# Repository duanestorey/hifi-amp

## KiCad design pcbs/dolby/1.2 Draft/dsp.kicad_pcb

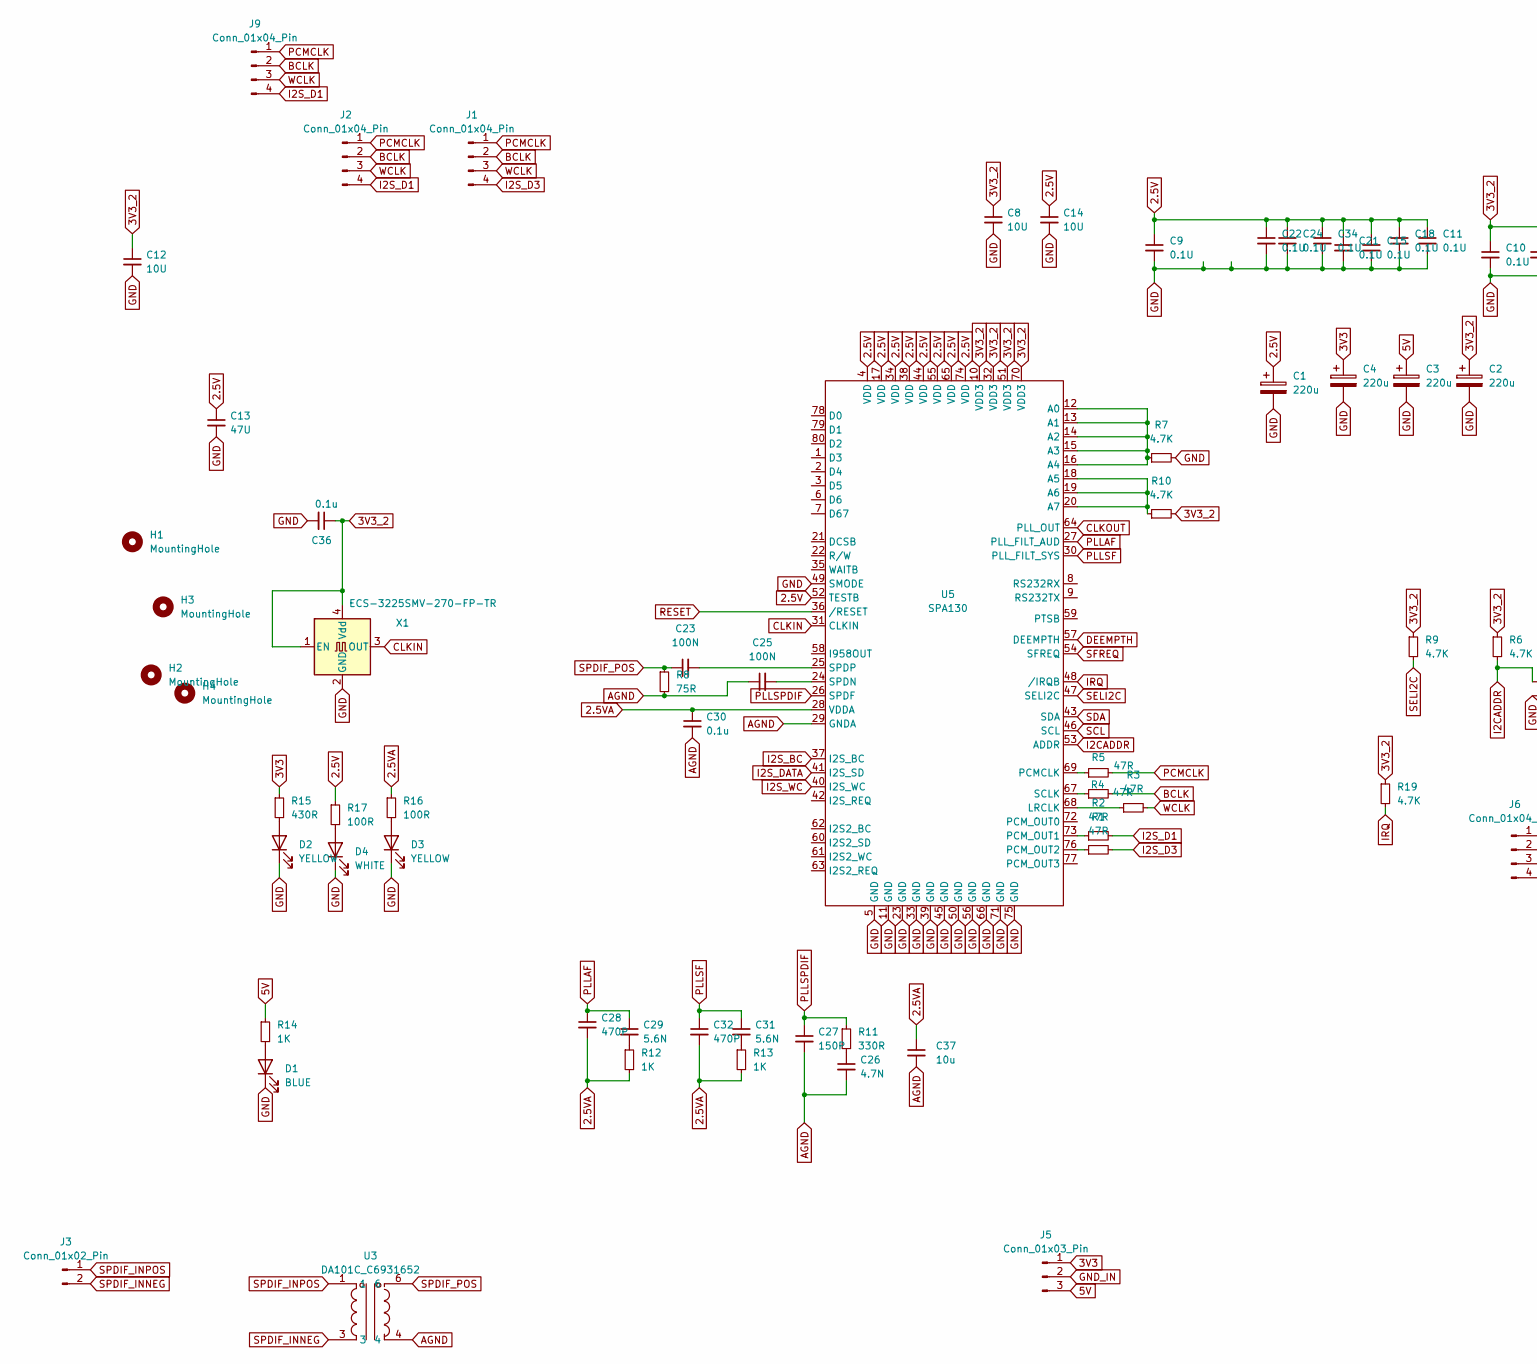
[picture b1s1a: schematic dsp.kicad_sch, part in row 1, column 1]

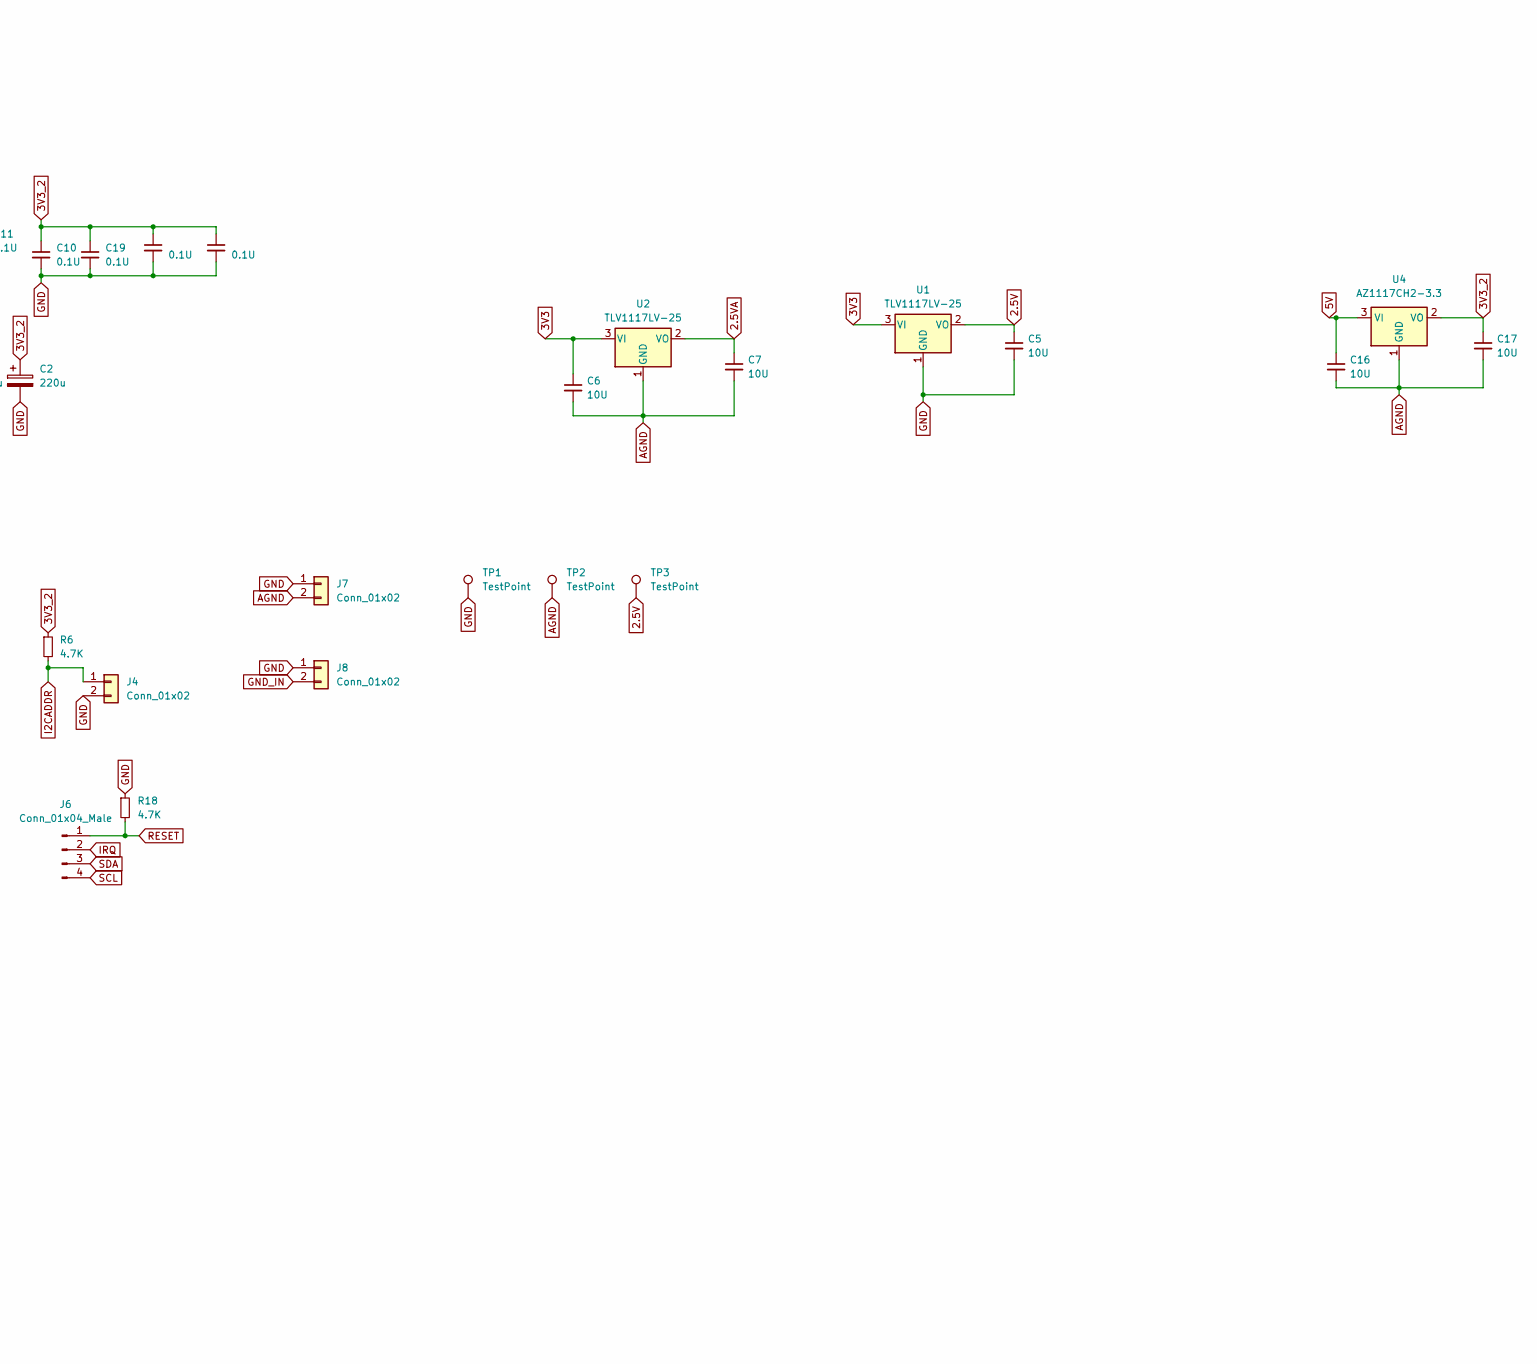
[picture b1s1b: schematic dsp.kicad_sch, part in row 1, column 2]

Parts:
C1, C2, C3, C4: 220u; CP_Radial_D6.3mm_P2.50mm
C5, C6, C7, C8, C12, C14, C16, C17: 10U; C_1206_3216Metric_Pad1.33x1.80mm_HandSolder
C9, C10, C11, C15, C18, C19, C20, C21, C22, C24, C33, C34: 0.1U; C_0805_2012Metric_Pad1.18x1.45mm_HandSolder
C13: 47U; C_1206_3216Metric_Pad1.33x1.80mm_HandSolder
C23, C25: 100N; C_0805_2012Metric_Pad1.18x1.45mm_HandSolder
C26: 4.7N; C_0805_2012Metric_Pad1.18x1.45mm_HandSolder
C27: 150P; C_0805_2012Metric_Pad1.18x1.45mm_HandSolder
C28, C32: 470P; C_0805_2012Metric_Pad1.18x1.45mm_HandSolder
C29, C31: 5.6N; C_0805_2012Metric_Pad1.18x1.45mm_HandSolder
C30, C36: 0.1u; C_0805_2012Metric_Pad1.18x1.45mm_HandSolder
C37: 10u; C_1206_3216Metric_Pad1.33x1.80mm_HandSolder
D1: BLUE; LED_0805_2012Metric_Pad1.15x1.40mm_HandSolder
D2, D3: YELLOW; LED_0805_2012Metric_Pad1.15x1.40mm_HandSolder
D4: WHITE; LED_0805_2012Metric_Pad1.15x1.40mm_HandSolder
H1, H2, H3, H4: MountingHole; MountingHole_3.2mm_M3_DIN965_Pad_TopBottom
J1, J2: Conn_01x04_Pin; JST_PH_B4B-PH-K_1x04_P2.00mm_Vertical
J3: Conn_01x02_Pin; JST_XH_B2B-XH-A_1x02_P2.50mm_Vertical
J4, J7, J8: Conn_01x02; PinHeader_1x02_P2.54mm_Vertical
J5: Conn_01x03_Pin; JST_PH_B3B-PH-K_1x03_P2.00mm_Vertical
J6: Conn_01x04_Male; JST_PH_B4B-PH-K_1x04_P2.00mm_Vertical
J9: Conn_01x04_Pin; PinHeader_1x04_P2.54mm_Vertical
R1, R2, R3, R4, R5: 47R; R_0805_2012Metric_Pad1.20x1.40mm_HandSolder
R6, R7, R9, R10, R18, R19: 4.7K; R_0603_1608Metric_Pad0.98x0.95mm_HandSolder
R8: 75R; R_0603_1608Metric_Pad0.98x0.95mm_HandSolder
R11: 330R; R_0603_1608Metric_Pad0.98x0.95mm_HandSolder
R12, R13, R14: 1K; R_0603_1608Metric_Pad0.98x0.95mm_HandSolder
R15: 430R; R_0603_1608Metric_Pad0.98x0.95mm_HandSolder
R16, R17: 100R; R_0603_1608Metric_Pad0.98x0.95mm_HandSolder
TP1, TP2, TP3: TestPoint; TestPoint_THTPad_1.5x1.5mm_Drill0.7mm
U1, U2: TLV1117LV-25; SOT-223-3_TabPin2
U3: DA101C_C6931652; XFMR-TH_4P-L9.5-W9.0-P5.08-LS10.2_C9900096976; LCSC Part C6931652
U4: AZ1117CH2-3.3; SOT-223-3_TabPin2
U5: SPA130; LQFP-80_14x14mm_P0.65mm
X1: ECS-3225SMV-270-FP-TR; Oscillator_SMD_EuroQuartz_XO32-4Pin_3.2x2.5mm_HandSoldering

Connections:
2.5V: C1.1, C5.1, C9.1, C11.1, C13.1, C14.1, C15.1, C18.1, C21.1, C22.1, C24.1, C34.1, R17.1, TP3.1, U1.2 (VO), U5.4 (VDD), U5.17 (VDD), U5.34 (VDD), U5.38 (VDD), U5.44 (VDD), U5.52 (TESTB), U5.55 (VDD), U5.65 (VDD), U5.74 (VDD)
2.5VA: C7.1, C28.2, C30.1, C32.2, C37.1, R12.2, R13.2, R16.1, U2.2 (VO), U5.28 (VDDA)
3V3: C4.1, C6.1, J5.1, R15.1, U1.3 (VI), U2.3 (VI)
3V3_2: C2.1, C8.1, C10.1, C12.1, C17.1, C19.1, C20.1, C33.1, C36.1, R6.1, R9.1, R10.2, R19.1, U4.2 (VO), U5.10 (VDD3), U5.32 (VDD3), U5.51 (VDD3), U5.70 (VDD3), X1.1 (EN), X1.4 (Vdd)
5V: C3.1, C16.1, J5.3, R14.1, U4.3 (VI)
AGND: C6.2, C7.2, C16.2, C17.2, C25.1, C26.2, C27.2, C30.2, C37.2, J7.2, R8.2, TP2.1, U2.1 (GND), U3.4, U4.1 (GND), U5.29 (GNDA)
BCLK: J1.2, J2.2, J9.2, R4.2
CLKIN: U5.31 (CLKIN), X1.3 (OUT)
CLKOUT: U5.64 (PLL_OUT)
DEEMPTH: U5.57 (DEEMPTH)
GND: C1.2, C2.2, C3.2, C4.2, C5.2, C8.2, C9.2, C10.2, C11.2, C12.2, C13.2, C14.2, C15.2, C18.2, C19.2, C20.2, C21.2, C22.2, C24.2, C33.2, C34.2, C36.2, D1.1 (K), D2.1 (K), D3.1 (K), D4.1 (K), J4.2, J7.1, J8.1, R7.2, R18.1, TP1.1, U1.1 (GND), U5.5 (GND), U5.11 (GND), U5.23 (GND), U5.33 (GND), U5.39 (GND), U5.45 (GND), U5.49 (SMODE), U5.50 (GND), U5.56 (GND), U5.66 (GND), U5.71 (GND), U5.75 (GND), X1.2 (GND)
GND_IN: J5.2, J8.2
I2CADDR: J4.1, R6.2, U5.53 (ADDR)
I2S_BC: U5.37 (I2S_BC)
I2S_D1: J2.4, J9.4, R2.2
I2S_D3: J1.4, R1.2
I2S_DATA: U5.41 (I2S_SD)
I2S_WC: U5.40 (I2S_WC)
IRQ: J6.2, R19.2, U5.48 (/IRQB)
unnamed: C26.1, R11.2
unnamed: C29.2, R12.1
unnamed: C31.2, R13.1
unnamed: D1.2 (A), R14.2
unnamed: D2.2 (A), R15.2
unnamed: D3.2 (A), R16.2
unnamed: D4.2 (A), R17.2
unnamed: R7.1, U5.12 (A0), U5.13 (A1), U5.14 (A2), U5.15 (A3), U5.16 (A4)
unnamed: R10.1, U5.18 (A5), U5.19 (A6), U5.20 (A7)
unnamed: R3.1, U5.68 (LRCLK)
unnamed: R5.1, U5.69 (PCMCLK)
unnamed: R2.1, U5.73 (PCM_OUT1)
unnamed: R1.1, U5.76 (PCM_OUT2)
unnamed: R4.1, U5.67 (SCLK)
unnamed: C25.2, U5.24 (SPDN)
unnamed: C23.2, U5.25 (SPDP)
PCMCLK: J1.1, J2.1, J9.1, R5.2
PLLAF: C28.1, C29.1, U5.27 (PLL_FILT_AUD)
PLLSF: C31.1, C32.1, U5.30 (PLL_FILT_SYS)
PLLSPDIF: C27.1, R11.1, U5.26 (SPDF)
RESET: J6.1, R18.2, U5.36 (/RESET)
SCL: J6.4, U5.46 (SCL)
SDA: J6.3, U5.43 (SDA)
SELI2C: R9.2, U5.47 (SELI2C)
SFREQ: U5.54 (SFREQ)
SPDIF_INNEG: J3.2, U3.3
SPDIF_INPOS: J3.1, U3.1
SPDIF_POS: C23.1, R8.1, U3.6
WCLK: J1.3, J2.3, J9.3, R3.2

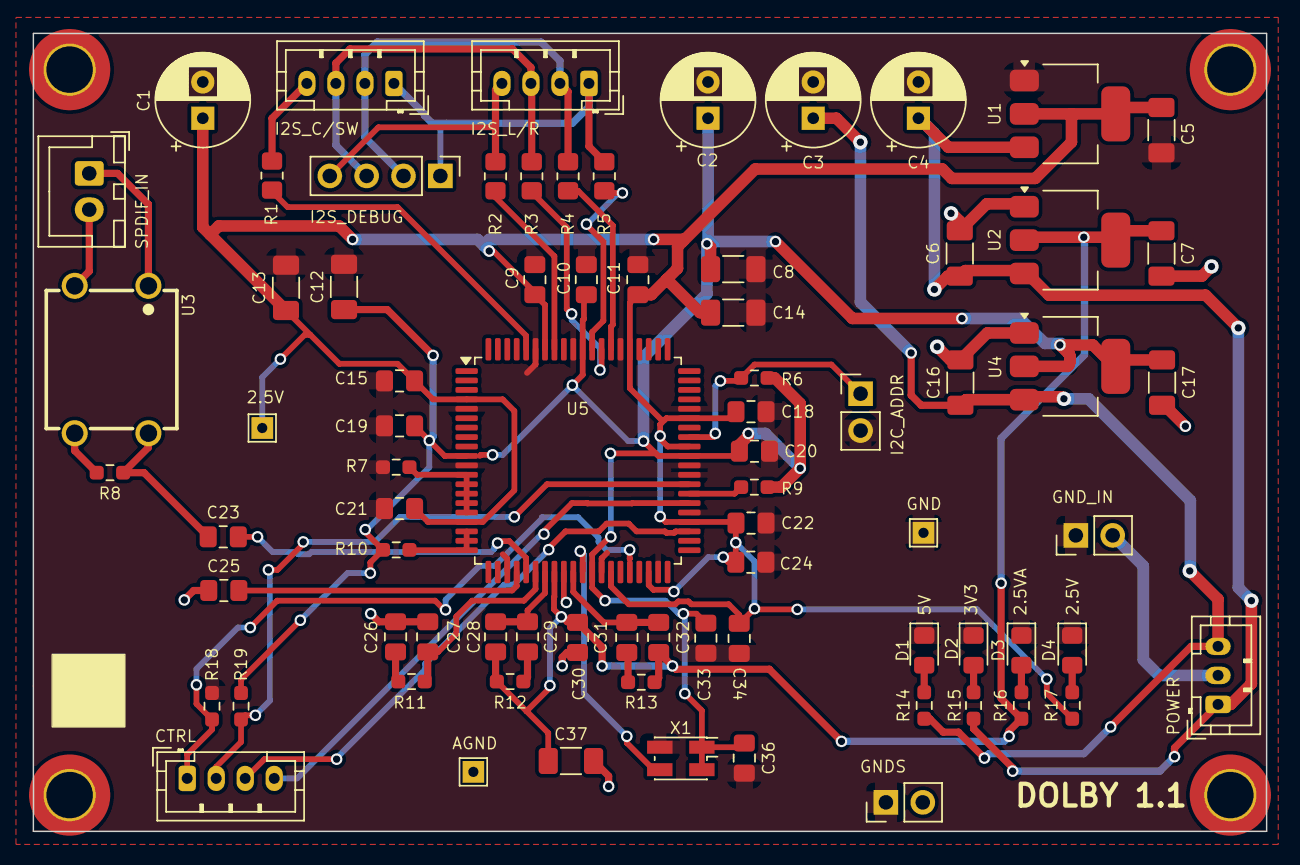
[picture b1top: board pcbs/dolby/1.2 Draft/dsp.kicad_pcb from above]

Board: 2 copper layers, 85.0 x 55.0 mm, 81 parts (0 on the bottom side), 42 nets.

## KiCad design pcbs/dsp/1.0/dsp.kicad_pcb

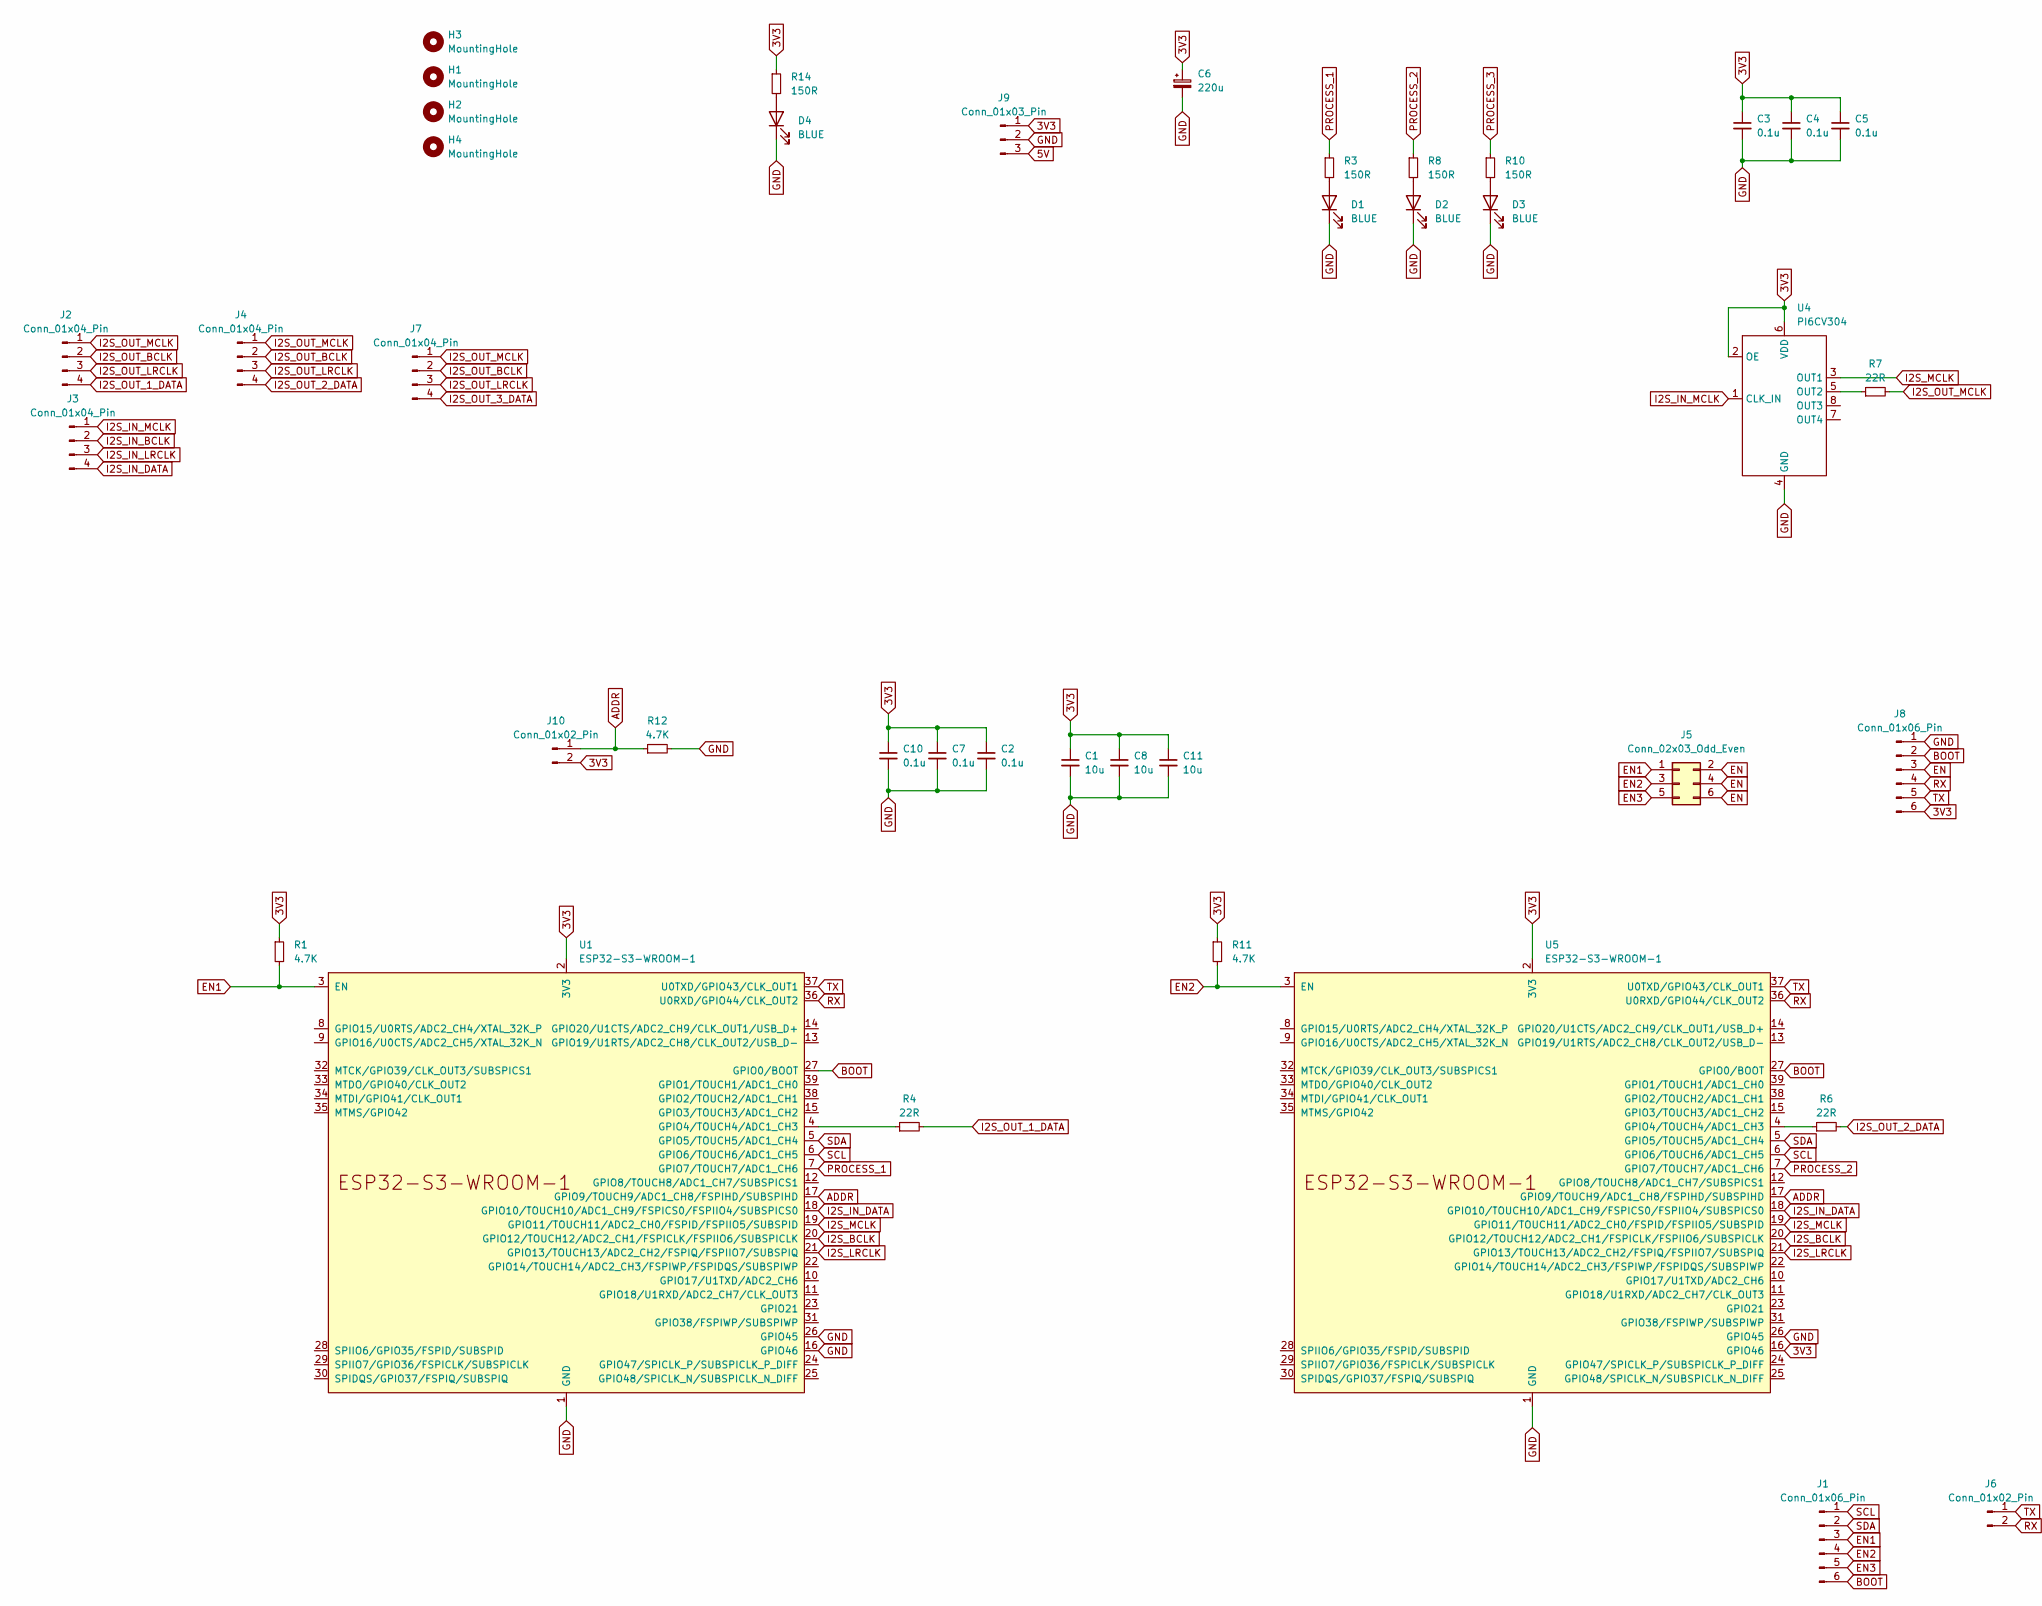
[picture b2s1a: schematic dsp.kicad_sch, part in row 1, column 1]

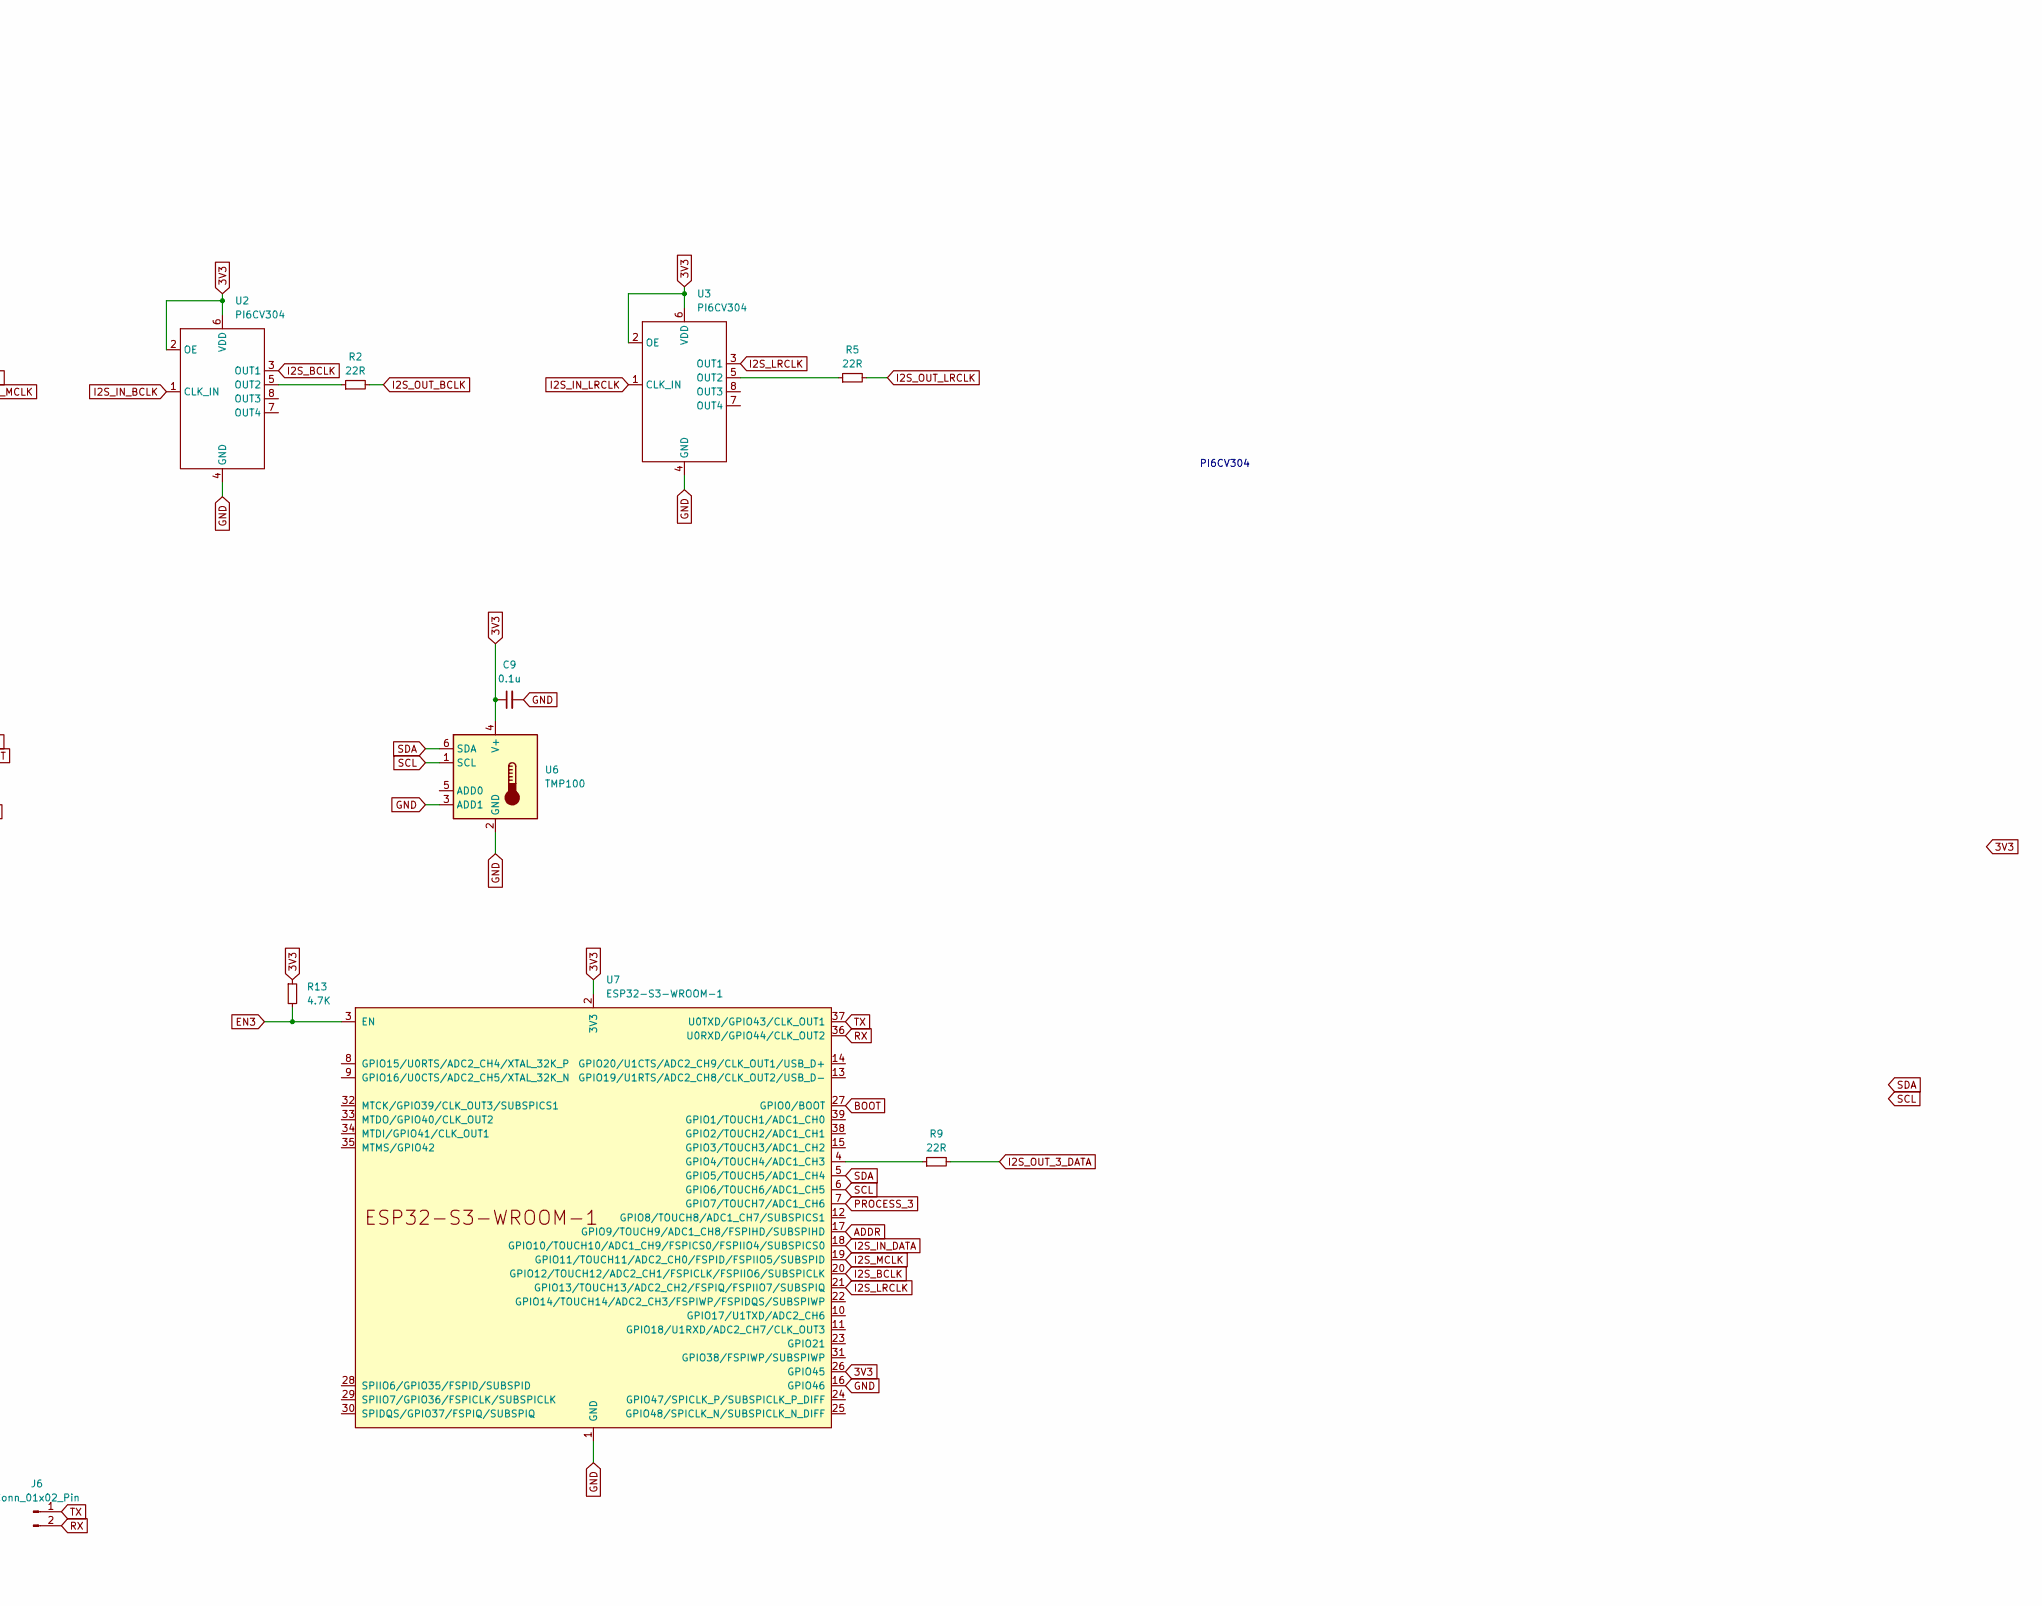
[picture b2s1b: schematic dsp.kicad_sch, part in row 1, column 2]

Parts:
C1, C8, C11: 10u; C_0805_2012Metric_Pad1.18x1.45mm_HandSolder
C2, C3, C4, C5, C7, C9, C10: 0.1u; C_0603_1608Metric_Pad1.08x0.95mm_HandSolder
C6: 220u; CP_Radial_D6.3mm_P2.50mm; LCSC C4747974
D1, D2, D3, D4: BLUE; D_0603_1608Metric; LCSC C84259
H1, H2, H3, H4: MountingHole; MountingHole_3.2mm_M3_DIN965_Pad_TopOnly
J1: Conn_01x06_Pin; JST_PH_B6B-PH-K_1x06_P2.00mm_Vertical
J2, J3, J4, J7: Conn_01x04_Pin; JST_PH_B4B-PH-K_1x04_P2.00mm_Vertical
J5: Conn_02x03_Odd_Even; PinHeader_2x03_P2.54mm_Vertical
J6: Conn_01x02_Pin; JST_PH_B2B-PH-K_1x02_P2.00mm_Vertical
J8: Conn_01x06_Pin; PinHeader_1x06_P2.54mm_Vertical
J9: Conn_01x03_Pin; JST_PH_B3B-PH-K_1x03_P2.00mm_Vertical
J10: Conn_01x02_Pin; PinHeader_1x02_P2.54mm_Vertical
R1, R11, R12, R13: 4.7K; R_0603_1608Metric; LCSC C23162
R2, R5, R7: 22R; R_0603_1608Metric
R3, R8, R10, R14: 150R; R_0603_1608Metric; LCSC C22808
R4, R9: 22R; R_0805_2012Metric; Mouser 603-RT0805FRE0722RL
R6: 22R; R_0805_2012Metric
U1, U5, U7: ESP32-S3-WROOM-1; Mouser 356-ESP32S3WRM1N16R8
U2, U3, U4: PI6CV304; TSSOP-8_4.4x3mm_P0.65mm
U6: TMP100; SOT-23-6

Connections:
3V3: C1.1, C2.1, C3.1, C4.1, C5.1, C6.1, C7.1, C8.1, C9.1, C10.1, C11.1, J8.6, J9.1, J10.2, R1.1, R11.1, R13.1, R14.1, U1.2 (3V3), U2.2 (OE), U2.6 (VDD), U3.2 (OE), U3.6 (VDD), U4.2 (OE), U4.6 (VDD), U5.2 (3V3), U5.16 (GPIO46), U6.4 (V+), U7.2 (3V3), U7.26 (GPIO45)
5V: J9.3
ADDR: J10.1, R12.1, U1.17 (GPIO9/TOUCH9/ADC1_CH8/FSPIHD/SUBSPIHD), U5.17 (GPIO9/TOUCH9/ADC1_CH8/FSPIHD/SUBSPIHD), U7.17 (GPIO9/TOUCH9/ADC1_CH8/FSPIHD/SUBSPIHD)
BOOT: J1.6, J8.2, U1.27 (GPIO0/BOOT), U5.27 (GPIO0/BOOT), U7.27 (GPIO0/BOOT)
EN: J5.2, J5.4, J5.6, J8.3
EN1: J1.3, J5.1, R1.2, U1.3 (EN)
EN2: J1.4, J5.3, R11.2, U5.3 (EN)
EN3: J1.5, J5.5, R13.2, U7.3 (EN)
GND: C1.2, C2.2, C3.2, C4.2, C5.2, C6.2, C7.2, C8.2, C9.2, C10.2, C11.2, D1.1 (K), D2.1 (K), D3.1 (K), D4.1 (K), J8.1, J9.2, R12.2, U1.1 (GND), U1.16 (GPIO46), U1.26 (GPIO45), U1.40 (GND), U1.41 (GND), U2.4 (GND), U3.4 (GND), U4.4 (GND), U5.1 (GND), U5.26 (GPIO45), U5.40 (GND), U5.41 (GND), U6.2 (GND), U6.3 (ADD1), U7.1 (GND), U7.16 (GPIO46), U7.40 (GND), U7.41 (GND)
I2S_BCLK: U1.20 (GPIO12/TOUCH12/ADC2_CH1/FSPICLK/FSPIIO6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), U2.3 (OUT1), U5.20 (GPIO12/TOUCH12/ADC2_CH1/FSPICLK/FSPIIO6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), U7.20 (GPIO12/TOUCH12/ADC2_CH1/FSPICLK/FSPIIO6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)
I2S_IN_BCLK: J3.2, U2.1 (CLK_IN)
I2S_IN_DATA: J3.4, U1.18 (GPIO10/TOUCH10/ADC1_CH9/FSPICS0/FSPIIO4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), U5.18 (GPIO10/TOUCH10/ADC1_CH9/FSPICS0/FSPIIO4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), U7.18 (GPIO10/TOUCH10/ADC1_CH9/FSPICS0/FSPIIO4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)
I2S_IN_LRCLK: J3.3, U3.1 (CLK_IN)
I2S_IN_MCLK: J3.1, U4.1 (CLK_IN)
I2S_LRCLK: U1.21 (GPIO13/TOUCH13/ADC2_CH2/FSPIQ/FSPIIO7/S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), U3.3 (OUT1), U5.21 (GPIO13/TOUCH13/ADC2_CH2/FSPIQ/FSPIIO7/S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), U7.21 (GPIO13/TOUCH13/ADC2_CH2/FSPIQ/FSPIIO7/S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)
I2S_MCLK: U1.19 (GPIO11/TOUCH11/ADC2_CH0/FSPID/FSPIIO5/S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), U4.3 (OUT1), U5.19 (GPIO11/TOUCH11/ADC2_CH0/FSPID/FSPIIO5/S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), U7.19 (GPIO11/TOUCH11/ADC2_CH0/FSPID/FSPIIO5/S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)
I2S_OUT_1_DATA: J2.4, R4.2
I2S_OUT_2_DATA: J4.4, R6.2
I2S_OUT_3_DATA: J7.4, R9.2
I2S_OUT_BCLK: J2.2, J4.2, J7.2, R2.2
I2S_OUT_LRCLK: J2.3, J4.3, J7.3, R5.2
I2S_OUT_MCLK: J2.1, J4.1, J7.1, R7.2
unnamed: D1.2 (A), R3.2
unnamed: D2.2 (A), R8.2
unnamed: D3.2 (A), R10.2
unnamed: D4.2 (A), R14.2
unnamed: R4.1, U1.4 (GPIO4/TOUCH4/ADC1_CH3)
unnamed: R2.1, U2.5 (OUT2)
unnamed: R5.1, U3.5 (OUT2)
unnamed: R7.1, U4.5 (OUT2)
unnamed: R6.1, U5.4 (GPIO4/TOUCH4/ADC1_CH3)
unnamed: R9.1, U7.4 (GPIO4/TOUCH4/ADC1_CH3)
PROCESS_1: R3.1, U1.7 (GPIO7/TOUCH7/ADC1_CH6)
PROCESS_2: R8.1, U5.7 (GPIO7/TOUCH7/ADC1_CH6)
PROCESS_3: R10.1, U7.7 (GPIO7/TOUCH7/ADC1_CH6)
RX: J6.2, J8.4, U1.36 (U0RXD/GPIO44/CLK_OUT2), U5.36 (U0RXD/GPIO44/CLK_OUT2), U7.36 (U0RXD/GPIO44/CLK_OUT2)
SCL: J1.1, U1.6 (GPIO6/TOUCH6/ADC1_CH5), U5.6 (GPIO6/TOUCH6/ADC1_CH5), U6.1 (SCL), U7.6 (GPIO6/TOUCH6/ADC1_CH5)
SDA: J1.2, U1.5 (GPIO5/TOUCH5/ADC1_CH4), U5.5 (GPIO5/TOUCH5/ADC1_CH4), U6.6 (SDA), U7.5 (GPIO5/TOUCH5/ADC1_CH4)
TX: J6.1, J8.5, U1.37 (U0TXD/GPIO43/CLK_OUT1), U5.37 (U0TXD/GPIO43/CLK_OUT1), U7.37 (U0TXD/GPIO43/CLK_OUT1)

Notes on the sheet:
PI6CV304

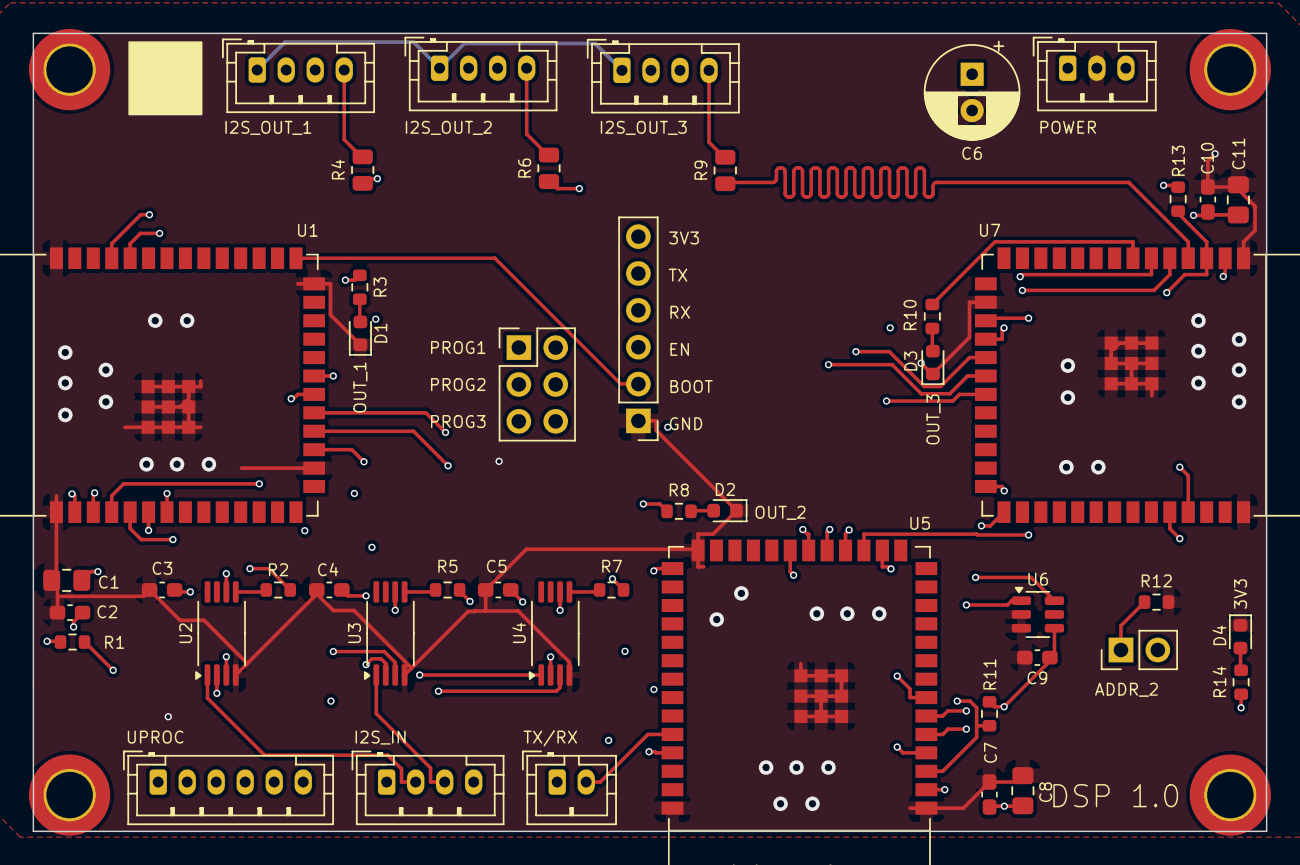
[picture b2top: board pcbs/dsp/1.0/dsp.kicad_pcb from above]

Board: 4 copper layers, 85.0 x 55.0 mm, 50 parts (0 on the bottom side), 38 nets.

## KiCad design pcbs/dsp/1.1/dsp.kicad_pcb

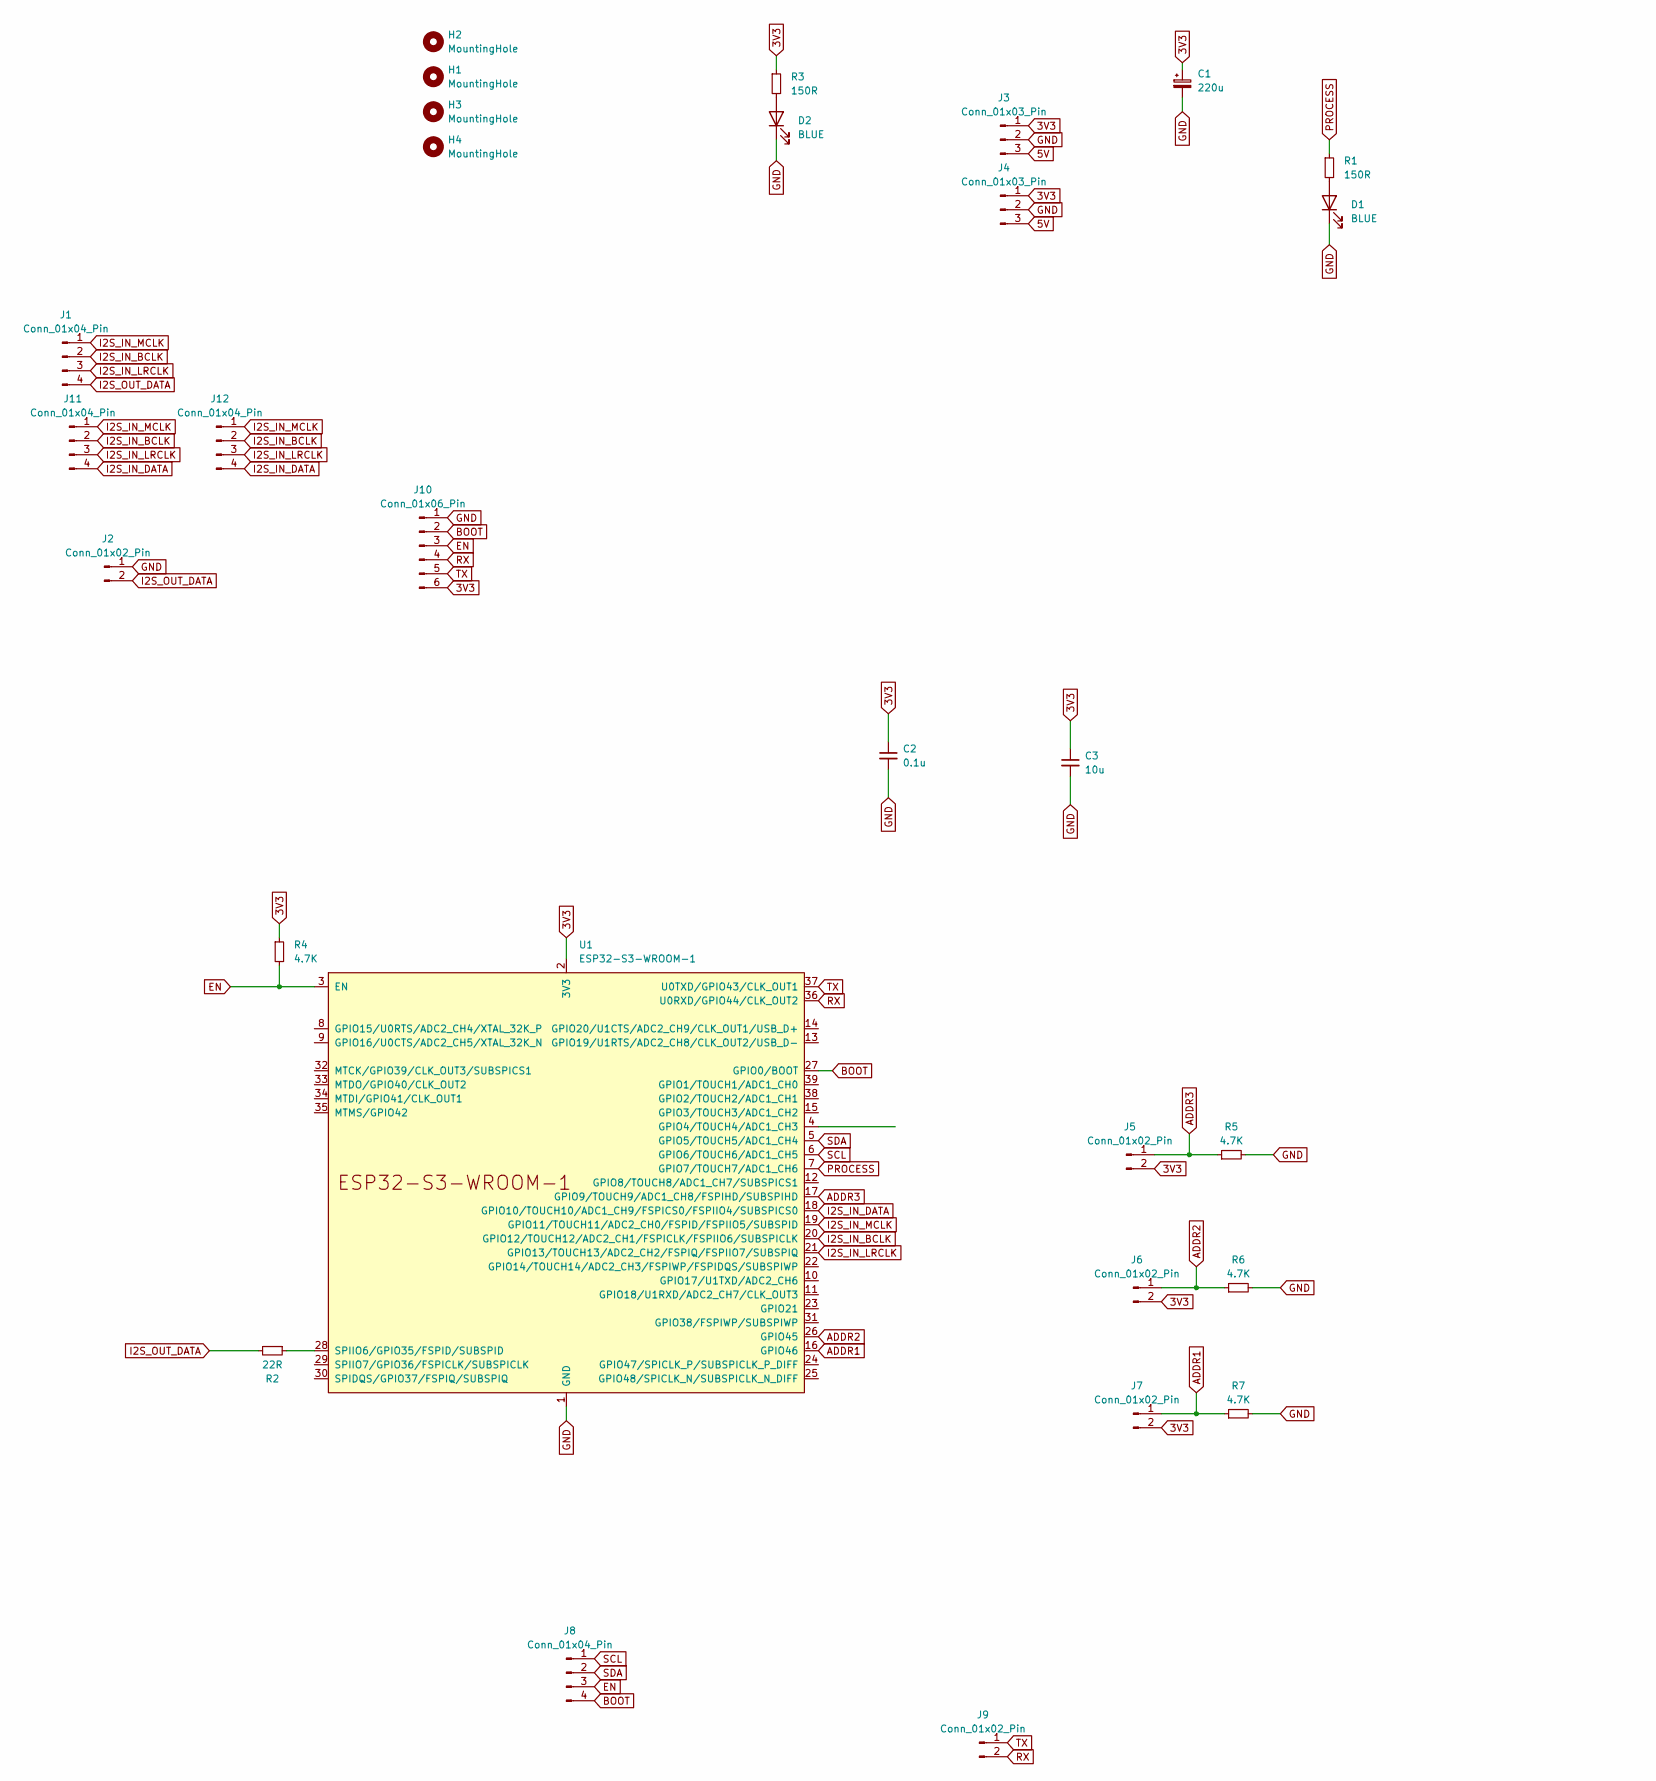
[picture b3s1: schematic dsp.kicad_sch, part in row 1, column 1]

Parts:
C1: 220u; CP_Radial_D6.3mm_P2.50mm; LCSC C4747974
C2: 0.1u; C_0603_1608Metric_Pad1.08x0.95mm_HandSolder
C3: 10u; C_0805_2012Metric_Pad1.18x1.45mm_HandSolder
D1, D2: BLUE; D_0603_1608Metric; LCSC C84259
H1, H2, H3, H4: MountingHole; MountingHole_3.2mm_M3_DIN965_Pad_TopOnly
J1, J8, J11, J12: Conn_01x04_Pin; JST_PH_B4B-PH-K_1x04_P2.00mm_Vertical
J2, J9: Conn_01x02_Pin; JST_PH_B2B-PH-K_1x02_P2.00mm_Vertical
J3, J4: Conn_01x03_Pin; JST_PH_B3B-PH-K_1x03_P2.00mm_Vertical
J5, J6, J7: Conn_01x02_Pin; PinHeader_1x02_P2.54mm_Vertical
J10: Conn_01x06_Pin; PinHeader_1x06_P2.54mm_Vertical
R1, R3: 150R; R_0603_1608Metric; LCSC C22808
R2: 22R; R_0805_2012Metric; Mouser 603-RT0805FRE0722RL
R4, R5, R6, R7: 4.7K; R_0603_1608Metric; LCSC C23162
U1: ESP32-S3-WROOM-1; Mouser 356-ESP32S3WRM1N16R8

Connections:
3V3: C1.1, C2.1, C3.1, J3.1, J4.1, J5.2, J6.2, J7.2, J10.6, R3.1, R4.1, U1.2 (3V3)
5V: J3.3, J4.3
ADDR1: J7.1, R7.1, U1.16 (GPIO46)
ADDR2: J6.1, R6.1, U1.26 (GPIO45)
ADDR3: J5.1, R5.1, U1.17 (GPIO9/TOUCH9/ADC1_CH8/FSPIHD/SUBSPIHD)
BOOT: J8.4, J10.2, U1.27 (GPIO0/BOOT)
EN: J8.3, J10.3, R4.2, U1.3 (EN)
GND: C1.2, C2.2, C3.2, D1.1 (K), D2.1 (K), J2.1, J3.2, J4.2, J10.1, R5.2, R6.2, R7.2, U1.1 (GND), U1.40 (GND), U1.41 (GND)
I2S_IN_BCLK: J1.2, J11.2, J12.2, U1.20 (GPIO12/TOUCH12/ADC2_CH1/FSPICLK/FSPIIO6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)
I2S_IN_DATA: J11.4, J12.4, U1.18 (GPIO10/TOUCH10/ADC1_CH9/FSPICS0/FSPIIO4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)
I2S_IN_LRCLK: J1.3, J11.3, J12.3, U1.21 (GPIO13/TOUCH13/ADC2_CH2/FSPIQ/FSPIIO7/S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)
I2S_IN_MCLK: J1.1, J11.1, J12.1, U1.19 (GPIO11/TOUCH11/ADC2_CH0/FSPID/FSPIIO5/S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)
I2S_OUT_DATA: J1.4, J2.2, R2.2
unnamed: D1.2 (A), R1.2
unnamed: D2.2 (A), R3.2
unnamed: R2.1, U1.28 (SPIIO6/GPIO35/FSPID/SUBSPID)
PROCESS: R1.1, U1.7 (GPIO7/TOUCH7/ADC1_CH6)
RX: J9.2, J10.4, U1.36 (U0RXD/GPIO44/CLK_OUT2)
SCL: J8.1, U1.6 (GPIO6/TOUCH6/ADC1_CH5)
SDA: J8.2, U1.5 (GPIO5/TOUCH5/ADC1_CH4)
TX: J9.1, J10.5, U1.37 (U0TXD/GPIO43/CLK_OUT1)

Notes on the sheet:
PI6CV304
